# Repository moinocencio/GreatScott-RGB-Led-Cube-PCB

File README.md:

# GreatScott-RGB-Led-Cube-PCB

Simple PCB made for a RGB LED Cube created by Great Scott (https://www.youtube.com/watch?v=EnM3p2TmWXc)

Some adaptations were made to adapt the project to my needs.

Work still in progress!

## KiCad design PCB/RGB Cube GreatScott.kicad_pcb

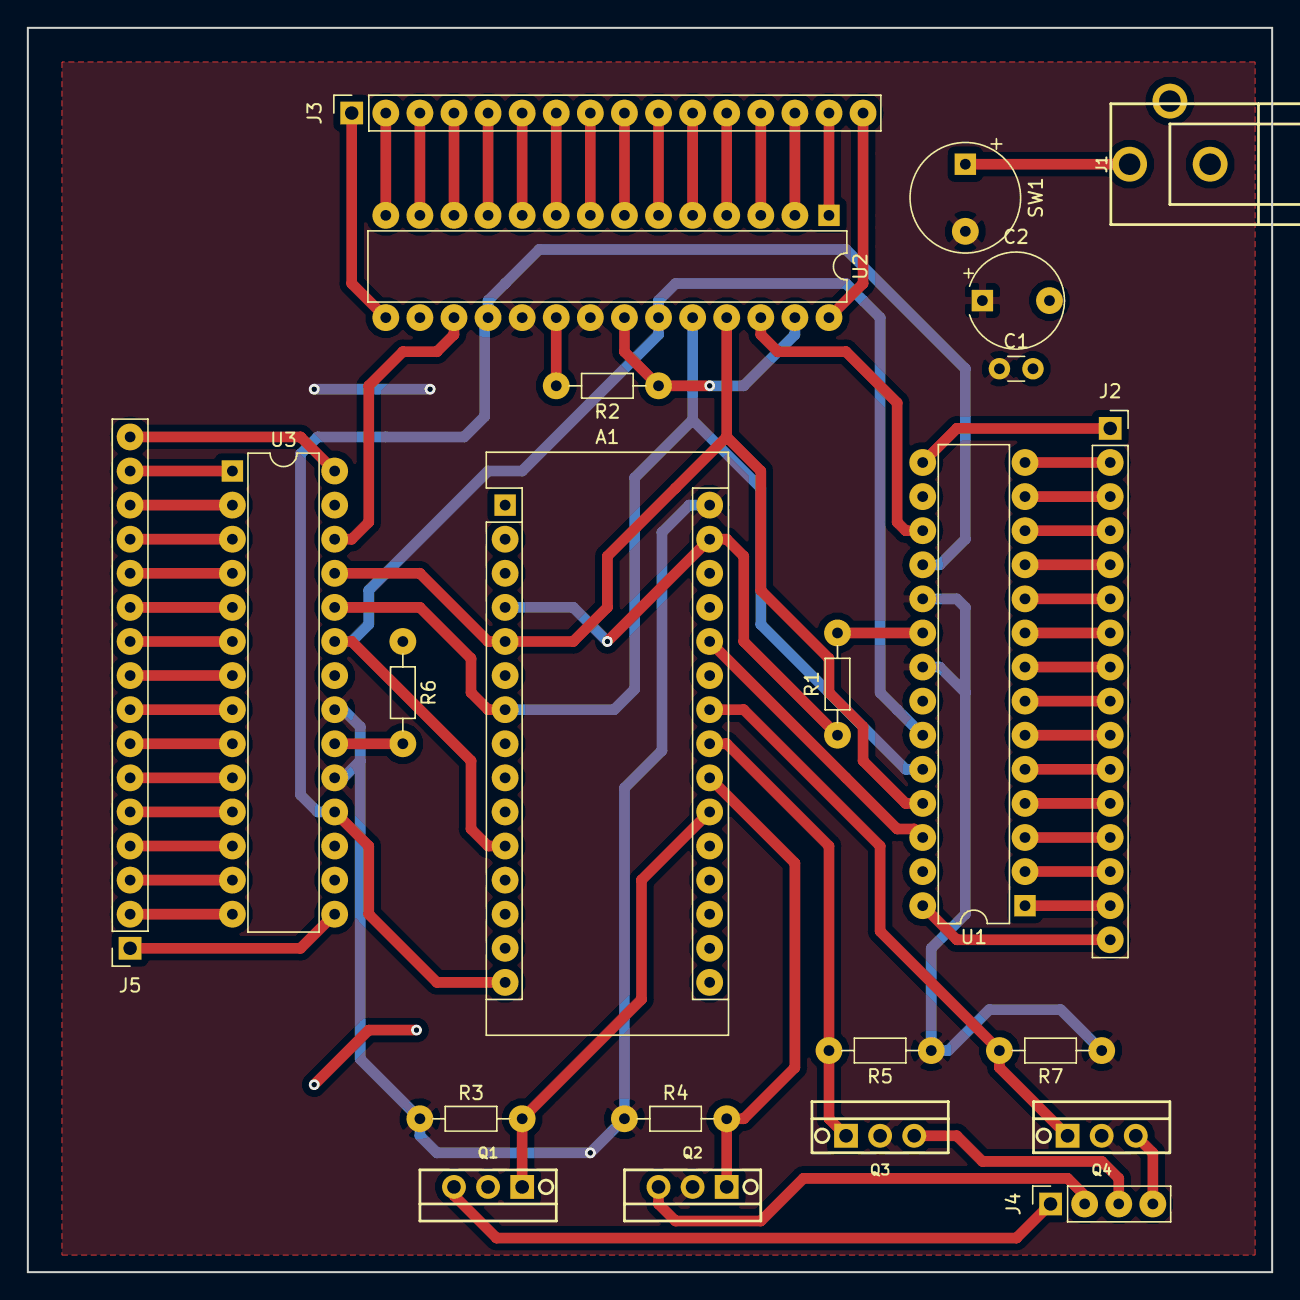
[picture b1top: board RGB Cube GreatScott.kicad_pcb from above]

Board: 2 copper layers, 92.7 x 92.7 mm, 23 parts (0 on the bottom side), 69 nets.

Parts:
A1: Arduino_Nano_v3.x; Arduino_Nano
C1: 100n; C_Disc_D3.0mm_W1.6mm_P2.50mm
C2: 100u; CP_Radial_Tantal_D7.0mm_P5.00mm
J1: Jack-DC; CUI-PJ-102A_dc-barrel-jack
J2, J3, J5: Conn_01x16_Female; PinSocket_1x16_P2.54mm_Vertical
J4: Conn_01x04_Female; PinSocket_1x04_P2.54mm_Vertical
Q1, Q2, Q3, Q4: IRF9540N; TO220_3pin
R1, R2, R6: 2k; R_Axial_DIN0204_L3.6mm_D1.6mm_P7.62mm_Horizontal
R3, R4, R5, R7: R; R_Axial_DIN0204_L3.6mm_D1.6mm_P7.62mm_Horizontal
SW1: SW_DPST_x2; CP_Radial_Tantal_D8.0mm_P5.00mm
U1, U2, U3: TLC5940NT; DIP-28_W7.62mm

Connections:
/BLANK: A1.11, U1.23, U2.23, U3.23
/GSCLK: A1.15, U1.18, U2.18, U3.18
/SCLK: A1.5, U1.25, U2.25, U3.25
/XLAT: A1.7, U1.24, U2.24, U3.24
GND: A1.4, A1.29, C1.2, C2.2, J1.2, R1.1, R2.1, R6.1, U1.22, U1.27, U2.22, U2.27, U3.22, U3.27
unnamed: A1.21, Q1.1, R3.2
unnamed: A1.22, Q2.1, R4.2
unnamed: A1.23, Q3.1, R5.2
unnamed: A1.24, Q4.1, R7.2
unnamed: A1.26, U1.26
unnamed: J1.1, SW1.1
unnamed: J2.1, U1.15
unnamed: J2.2, U1.14
unnamed: J2.3, U1.13
unnamed: J2.4, U1.12
unnamed: J2.5, U1.11
unnamed: J2.6, U1.10
unnamed: J2.7, U1.9
unnamed: J2.8, U1.8
unnamed: J2.9, U1.7
unnamed: J2.10, U1.6
unnamed: J2.11, U1.5
unnamed: J2.12, U1.4
unnamed: J2.13, U1.3
unnamed: J2.14, U1.2
unnamed: J2.15, U1.1
unnamed: J2.16, U1.28
unnamed: J3.1, U2.15
unnamed: J3.2, U2.14
unnamed: J3.3, U2.13
unnamed: J3.4, U2.12
unnamed: J3.5, U2.11
unnamed: J3.6, U2.10
unnamed: J3.7, U2.9
unnamed: J3.8, U2.8
unnamed: J3.9, U2.7
unnamed: J3.10, U2.6
unnamed: J3.11, U2.5
unnamed: J3.12, U2.4
unnamed: J3.13, U2.3
unnamed: J3.14, U2.2
unnamed: J3.15, U2.1
unnamed: J3.16, U2.28
unnamed: J4.1, Q1.3
unnamed: J4.2, Q2.3
unnamed: J4.3, Q3.3
unnamed: J4.4, Q4.3
unnamed: J5.1, U3.15
unnamed: J5.2, U3.14
unnamed: J5.3, U3.13
unnamed: J5.4, U3.12
unnamed: J5.5, U3.11
unnamed: J5.6, U3.10
unnamed: J5.7, U3.9
unnamed: J5.8, U3.8
unnamed: J5.9, U3.7
unnamed: J5.10, U3.6
unnamed: J5.11, U3.5
unnamed: J5.12, U3.4
unnamed: J5.13, U3.3
unnamed: J5.14, U3.2
unnamed: J5.15, U3.1
unnamed: J5.16, U3.28
unnamed: R1.2, U1.20
unnamed: R2.2, U2.20
unnamed: R6.2, U3.20
unnamed: U1.17, U2.26
unnamed: U2.17, U3.26
VCC: A1.30, C1.1, C2.1, Q1.2, Q2.2, Q3.2, Q4.2, R3.1, R4.1, R5.1, R7.1, SW1.2, U1.19, U1.21, U2.19, U2.21, U3.19, U3.21

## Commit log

2019-01-08 Added PCB Files
